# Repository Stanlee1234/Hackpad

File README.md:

# Hackable Hackpad!
So hello! I finished my personal hackpad!

I got my inspiration because this is the final project that I needed to make to qualify for Prototype. Even though I thought it was going to be pretty boring, I still powered on, and I found out that it was super fun to make!

I did face some challenges, though. At first, my KiCAD file was broken and somehow corrupted so I had to reset the project. Another thing is that it is my first time using Fusion 360, so I had to Google a few things. Other than that, I honestly did not face any major challenges.

## Here is my BOM:
- 1x XIAO RP2040
- 6x Cherry MX Switches
- 4x SK6812 MINI Leds
- 6x Blank DSA Keycaps
- 4x M3x16 Bolt
- 4x M3 Heatset

Good thing that I have a Bambu Lab A1! Now I don't need to wait for it to be accepted for me to get it printed.

Schematic!            |  PCB!         |   Case!
:-------------------------:|:-------------------------:|:-------------------------:|
 |  |

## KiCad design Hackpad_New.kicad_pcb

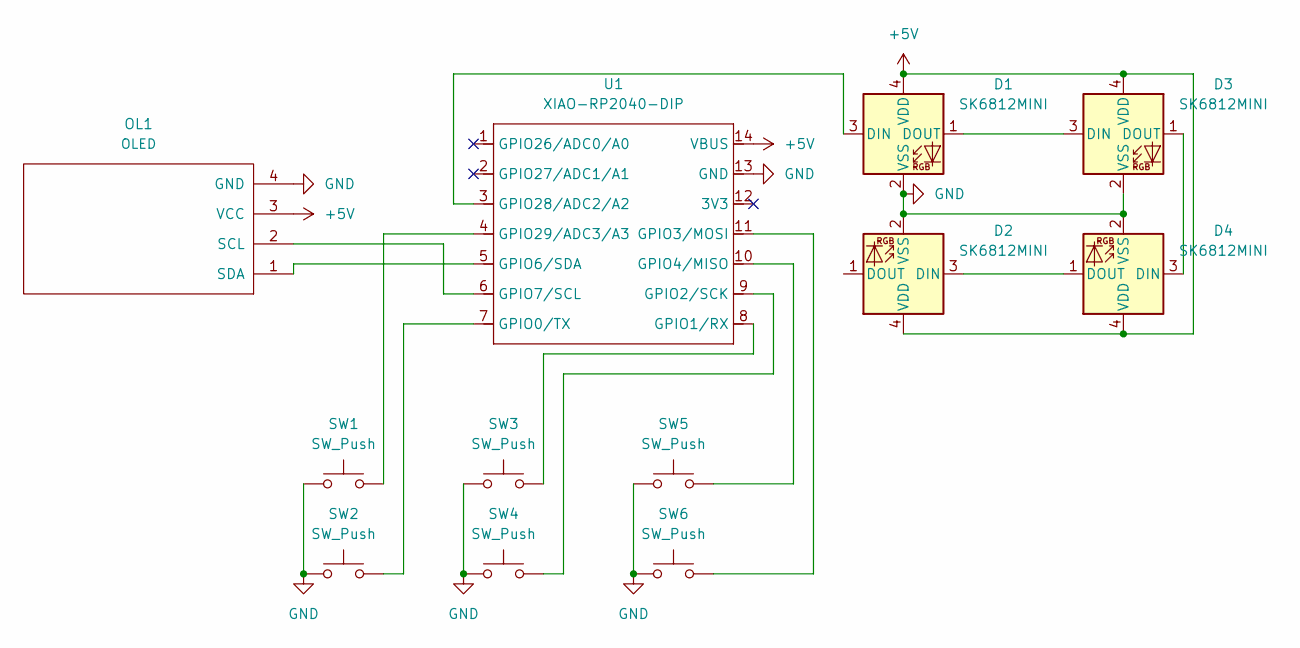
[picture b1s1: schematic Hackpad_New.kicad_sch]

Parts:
D1, D2, D3, D4: SK6812MINI; LED_SK6812MINI_PLCC4_3.5x3.5mm_P1.75mm
OL1: OLED; SSD1306-0.91-OLED-4pin-128x32 (1)
SW1, SW2, SW3, SW4, SW5, SW6: SW_Push; SW_Cherry_MX_1.00u_PCB
U1: XIAO-RP2040-DIP

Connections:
+5V: D1.4 (VDD), D2.4 (VDD), D3.4 (VDD), D4.4 (VDD), OL1.3 (VCC), U1.14 (VBUS)
GND: D1.2 (VSS), D2.2 (VSS), D3.2 (VSS), D4.2 (VSS), OL1.4 (GND), SW1.1, SW2.1, SW3.1, SW4.1, SW5.1, SW6.1, U1.13 (GND)
unnamed: D1.3 (DIN), U1.3 (GPIO28/ADC2/A2)
unnamed: D1.1 (DOUT), D3.3 (DIN)
unnamed: D2.3 (DIN), D4.1 (DOUT)
unnamed: D3.1 (DOUT), D4.3 (DIN)
unnamed: OL1.2 (SCL), U1.6 (GPIO7/SCL)
unnamed: OL1.1 (SDA), U1.5 (GPIO6/SDA)
unnamed: SW2.2, U1.7 (GPIO0/TX)
unnamed: SW3.2, U1.8 (GPIO1/RX)
unnamed: SW4.2, U1.9 (GPIO2/SCK)
unnamed: SW6.2, U1.11 (GPIO3/MOSI)
unnamed: SW5.2, U1.10 (GPIO4/MISO)
unnamed: SW1.2, U1.4 (GPIO29/ADC3/A3)

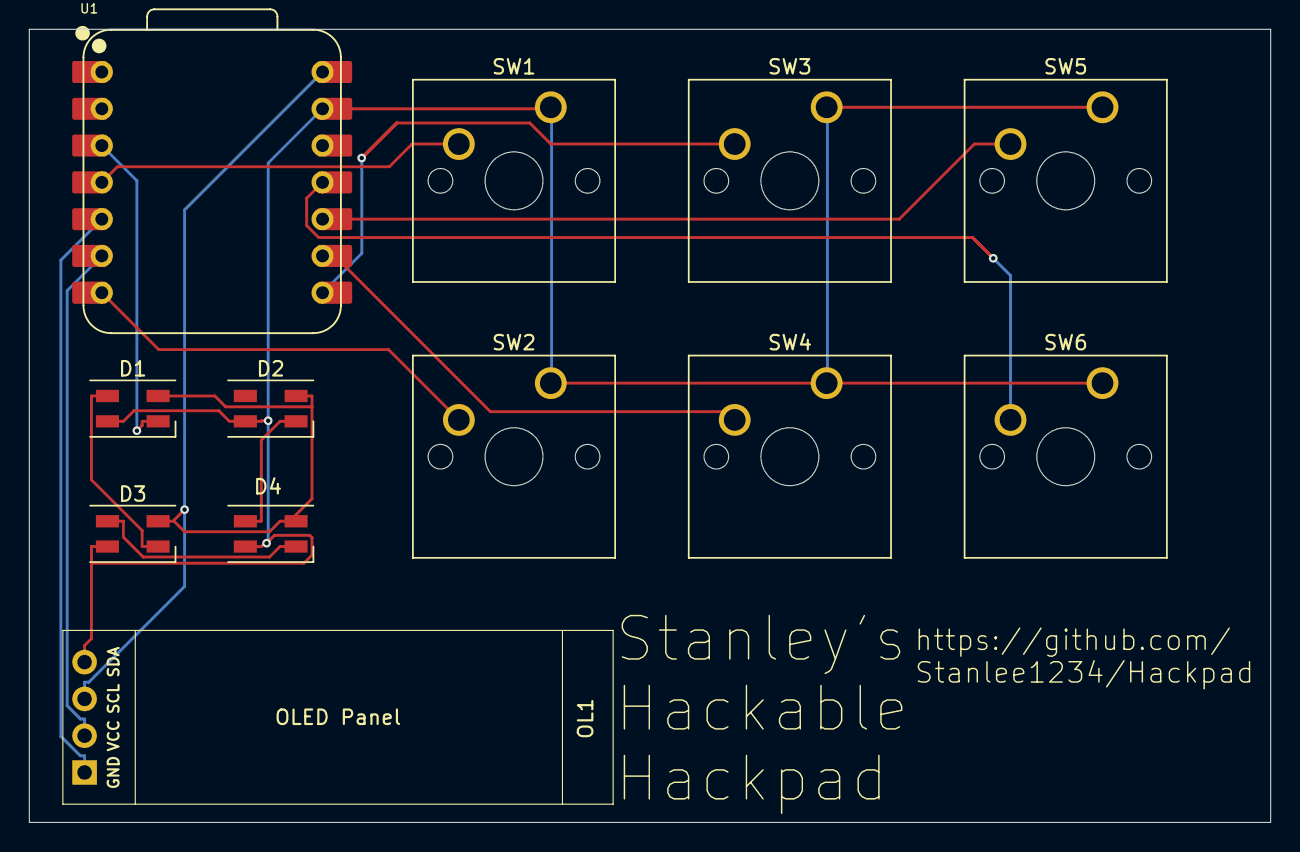
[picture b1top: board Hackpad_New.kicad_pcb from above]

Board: 2 copper layers, 85.7 x 54.8 mm, 12 parts (0 on the bottom side), 14 nets.

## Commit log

2025-11-24 Add initial README with project description
2025-11-24 Revise README with project details and BOM
    Updated README to reflect project completion and added BOM.
2025-11-24 Added KMK file
2025-11-24 Replace case image in README.md
    Updated image for the case section in README.
2025-11-24 Upload
